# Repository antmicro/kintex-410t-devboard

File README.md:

# Kintex K410T Devboard

Copyright (c) 2022-2025 [Antmicro](https://www.antmicro.com)

## Overview

This repository contains open hardware design files for a devkit created for AMD-Xilinx [Kintex-7 K410T](https://www.xilinx.com/products/silicon-devices/fpga/kintex-7.html) FPGA.

This development board routes the I/O interfaces from the SoM and provides the necessary power buses.
The design files were prepared in KiCad 7.

## Repository structure

The main repository directory contains KiCad PCB project files, a [LICENSE](LICENSE), and a README.
The remaining files are stored in the following directories:

* `doc` - contains generated schematics and other documentation
* `img` - contains graphics for this README
* `assets` - contains visual assets for showcasing the board on Antmicro [Open Hardware Portal](https://openhardware.antmicro.com)

## Key features

* AMD-Xilinx Kintex-7 K410T FPGA
* 512MB of DDR3L memory
* 256MB of SPI NOR flash
* 8MB of SRAM memory
* Assembly option for 2x QSPI
* Gigabit Ethernet
* HDMI output
* USB Type-C connector for FTDI JTAG and debug
* 2x PMOD
* FMC+ connector

## Block diagram

## Licensing

This project is published under the [Apache-2.0](LICENSE) license.

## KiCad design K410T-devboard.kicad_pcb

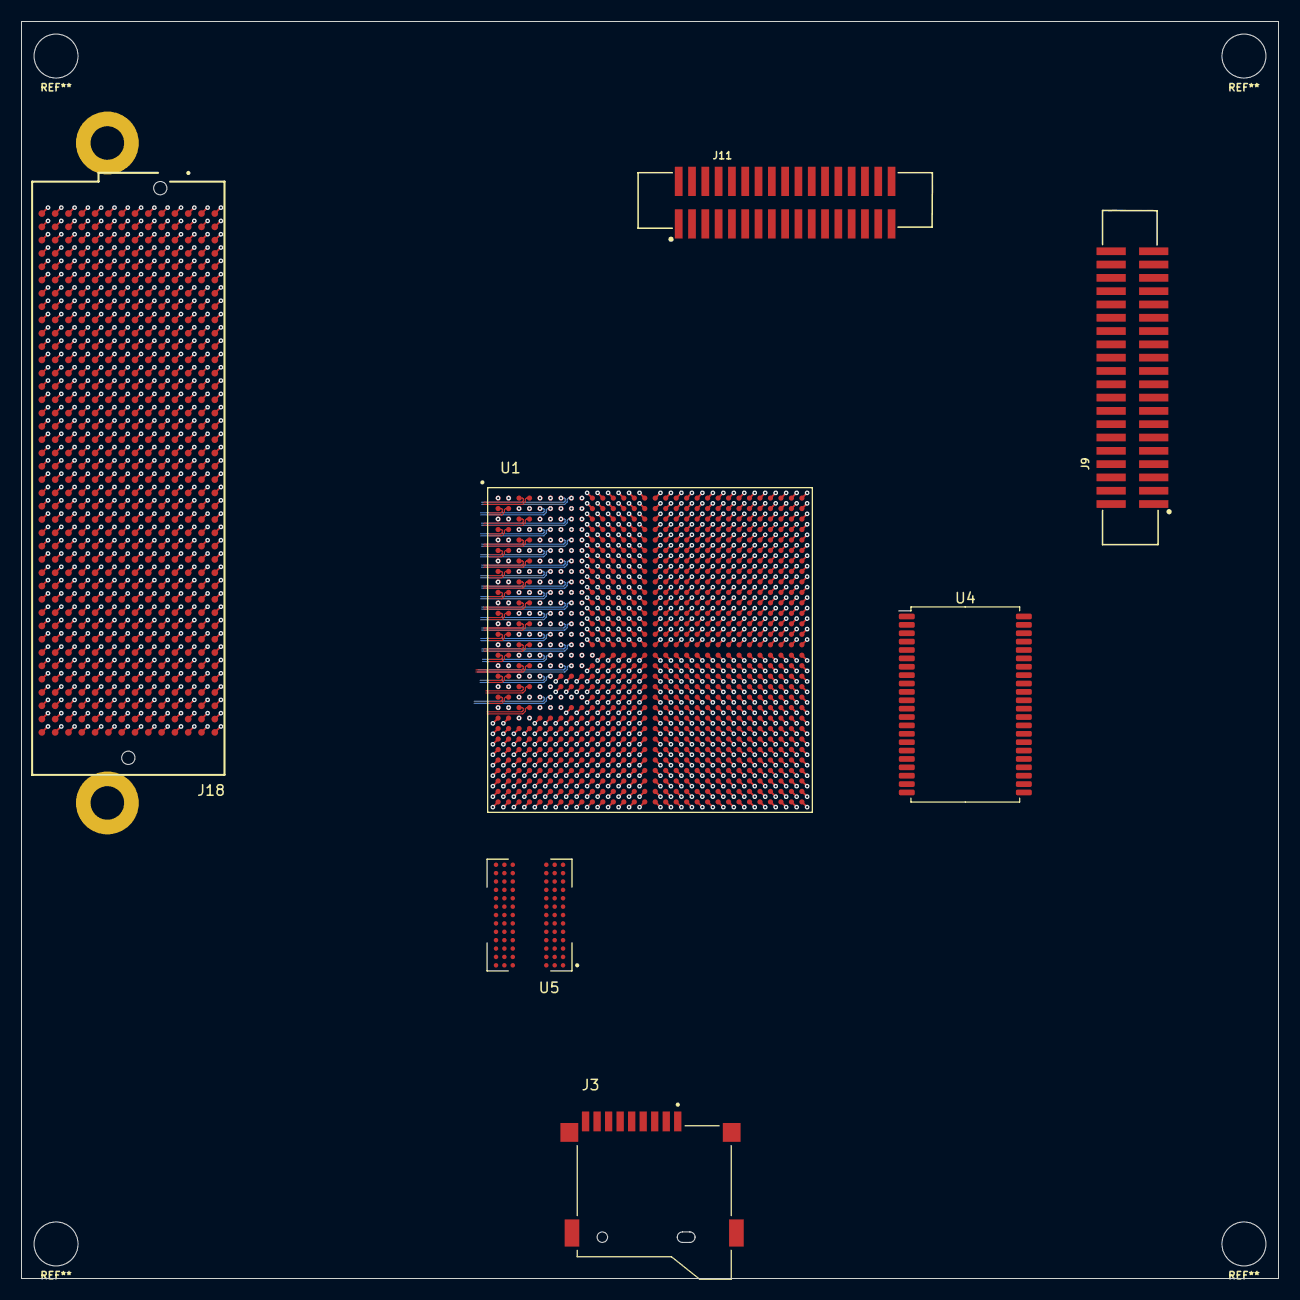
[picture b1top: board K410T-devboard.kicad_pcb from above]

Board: 10 copper layers, 120.0 x 120.0 mm, 7 parts (0 on the bottom side), 213 nets.

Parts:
J3: 693071020811; WE_693071020811
J9: 62704020621; 627x4020621
J11: 62703420621; 627x3420621
J18: ASP-184329-01_mounting_holes_FMCPinout; ASP-184329-01_mounting_holes
U1: XC7K410T-2FFG900I; xc7k410t-2ffg900I
U4: AS6C8008-55ZIN; TSOP-II-44_10.16x18.41mm_P0.8mm
U5: MT41K512M8DA; Micron_FBGA-78

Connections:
3V3_SYS: J18.C39 (3P3V), J18.D36 (3P3V), J18.D38 (3P3V), J18.D40 (3P3V)
12P0V: J18.C35 (12P0V), J18.C37 (12P0V)
+0V675_VREF: U5.E1 (VREFDQ), U5.J8 (VREFCA)
+0V675_VTT: U1.AD7 (IO_L6N_T0_VREF_34), U1.AG8 (IO_L19N_T3_VREF_34)
+1V0: U1.M11 (VCCINT), U1.M13 (VCCINT), U1.M15 (VCCINT), U1.M17 (VCCINT), U1.N10 (VCCINT), U1.N12 (VCCINT), U1.N14 (VCCINT), U1.N16 (VCCBRAM), U1.N18 (VCCINT), U1.P11 (VCCINT), U1.P17 (VCCINT), U1.R10 (VCCINT), U1.R12 (VCCINT), U1.R16 (VCCBRAM), U1.R18 (VCCINT), U1.T11 (VCCINT), U1.T17 (VCCINT), U1.U10 (VCCINT), U1.U12 (VCCINT), U1.U16 (VCCBRAM), U1.U18 (VCCINT), U1.V17 (VCCINT), U1.W16 (VCCBRAM), U1.W18 (VCCINT)
+1V2_MGTAVCC: U1.B7 (MGTAVCC), U1.D7 (MGTAVCC), U1.F7 (MGTAVCC), U1.H7 (MGTAVCC), U1.K7 (MGTAVCC), U1.M7 (MGTAVCC), U1.P7 (MGTAVCC)
+1V2_MGTAVTT: U1.B3 (MGTAVTT), U1.C5 (MGTAVTT), U1.D3 (MGTAVTT), U1.E5 (MGTAVTT), U1.F3 (MGTAVTT), U1.G5 (MGTAVTT), U1.H3 (MGTAVTT), U1.J5 (MGTAVTT), U1.K3 (MGTAVTT), U1.L5 (MGTAVTT), U1.M3 (MGTAVTT), U1.N5 (MGTAVTT), U1.P3 (MGTAVTT), U1.R5 (MGTAVTT), U1.T3 (MGTAVTT), U1.U5 (MGTAVTT), U1.V3 (MGTAVTT), U1.W5 (MGTAVTT), U1.W7 (MGTAVTTRCAL_115)
+1V8: U1.AA9 (VCCO_33), U1.AA19 (VCCO_32), U1.AB16 (VCCO_32), U1.AC13 (VCCO_33), U1.AD10 (VCCO_33), U1.AE17 (VCCO_32), U1.AF14 (VCCO_32), U1.AG11 (VCCO_33), U1.AH18 (VCCO_32), U1.AJ15 (VCCO_32), U1.AK12 (VCCO_33), U1.P13 (VCCAUX), U1.T7 (MGTVCCAUX), U1.T13 (VCCAUX), U1.V7 (MGTVCCAUX), U1.V11 (VCCAUX_IO_G0), U1.V13 (VCCAUX), U1.V15 (VCCAUX), U1.W10 (VCCAUX_IO_G0), U1.W12 (VCCAUX_IO_G0), U1.W14 (VCCAUX), U1.Y12 (VCCO_33)
+1V35: U1.AC3 (VCCO_34), U1.AE7 (VCCO_34), U1.AF4 (VCCO_34), U1.AG1 (VCCO_34), U1.AH8 (VCCO_34), U1.AJ5 (VCCO_34), U1.AK2 (VCCO_34), U5.A2 (VDD), U5.A9 (VDD), U5.B9 (VDDQ), U5.C1 (VDDQ), U5.D7 (VDD), U5.E2 (VDDQ), U5.E9 (VDDQ), U5.G2 (VDD), U5.G8 (VDD), U5.K1 (VDD), U5.K9 (VDD), U5.M1 (VDD), U5.M9 (VDD)
+3V3: J3.4 (VDD), J9.22, J11.22, U1.AA29 (VCCO_13), U1.AB6 (VCCO_0), U1.AB26 (VCCO_13), U1.AC23 (VCCO_12), U1.AD20 (VCCO_12), U1.AD30 (VCCO_13), U1.AE27 (VCCO_13), U1.AF24 (VCCO_12), U1.AG21 (VCCO_12), U1.AH28 (VCCO_13), U1.AJ25 (VCCO_13), U1.AK22 (VCCO_12), U1.P30 (VCCO_14), U1.R27 (VCCO_14), U1.T9 (VCCO_0), U1.T24 (VCCO_14), U1.U21 (VCCO_14), U1.V28 (VCCO_14), U1.W25 (VCCO_14), U1.Y22 (VCCO_12), U4.11 (VCC), U4.33 (VCC)
/DRAM + SRAM/DDR.A0: U1.AE4 (IO_L10P_T1_34), U5.K3 (A0)
/DRAM + SRAM/DDR.A1: U1.AG3 (IO_L9N_T1_DQS_34), U5.L7 (A1)
/DRAM + SRAM/DDR.A2: U1.AG4 (IO_L9P_T1_DQS_34), U5.L3 (A2)
/DRAM + SRAM/DDR.A3: U1.AF1 (IO_L8N_T1_34), U5.K2 (A3)
/DRAM + SRAM/DDR.A4: U1.AE1 (IO_L8P_T1_34), U5.L8 (A4)
/DRAM + SRAM/DDR.A5: U1.AF2 (IO_L7N_T1_34), U5.L2 (A5)
/DRAM + SRAM/DDR.A6: U1.AF3 (IO_L7P_T1_34), U5.M8 (A6)
/DRAM + SRAM/DDR.A7: U1.AC7 (IO_L6P_T0_34), U5.M2 (A7)
/DRAM + SRAM/DDR.A8: U1.AE6 (IO_L5N_T0_34), U5.N8 (A8)
/DRAM + SRAM/DDR.A9: U1.AD6 (IO_L5P_T0_34), U5.M3 (A9)
/DRAM + SRAM/DDR.A10: U1.AC4 (IO_L4N_T0_34), U5.H7 (A10/AP)
/DRAM + SRAM/DDR.A11: U1.AC5 (IO_L4P_T0_34), U5.M7 (A11)
/DRAM + SRAM/DDR.A12: U1.AC1 (IO_L2N_T0_34), U5.K7 (A12/BC#)
/DRAM + SRAM/DDR.A13: U1.AC2 (IO_L2P_T0_34), U5.N3 (A13)
/DRAM + SRAM/DDR.A14: U1.AD3 (IO_L1N_T0_34), U5.N7 (A14)
/DRAM + SRAM/DDR.A15: U1.AD4 (IO_L1P_T0_34), U5.J7 (A15)
/DRAM + SRAM/DDR.BA0: U1.AF5 (IO_L11N_T1_SRCC_34), U5.J2 (BA0)
/DRAM + SRAM/DDR.BA1: U1.AE5 (IO_L11P_T1_SRCC_34), U5.K8 (BA1)
/DRAM + SRAM/DDR.BA2: U1.AE3 (IO_L10N_T1_34), U5.J3 (BA2)
/DRAM + SRAM/DDR.CKE: U1.AH2 (IO_L16P_T2_34), U5.G9 (CKE)
/DRAM + SRAM/DDR.CK_N: U1.AD1 (IO_L3N_T0_DQS_34), U5.G7 (CK#)
/DRAM + SRAM/DDR.CK_P: U1.AD2 (IO_L3P_T0_DQS_34), U5.F7 (CK)
/DRAM + SRAM/DDR.DM: U1.AF8 (IO_L19P_T3_34), U5.B7 (DM/TDQS)
/DRAM + SRAM/DDR.DQ0: U1.AK5 (IO_L24P_T3_34), U5.B3 (DQ0)
/DRAM + SRAM/DDR.DQ1: U1.AK8 (IO_L23N_T3_34), U5.C7 (DQ1)
/DRAM + SRAM/DDR.DQ2: U1.AK6 (IO_L22N_T3_34), U5.C2 (DQ2)
/DRAM + SRAM/DDR.DQ3: U1.AJ6 (IO_L22P_T3_34), U5.C8 (DQ3)
/DRAM + SRAM/DDR.DQ4: U1.AG7 (IO_L20N_T3_34), U5.E3 (NF/DQ4)
/DRAM + SRAM/DDR.DQ5: U1.AJ8 (IO_L23P_T3_34), U5.E8 (NF/DQ5)
/DRAM + SRAM/DDR.DQ6: U1.AK4 (IO_L24N_T3_34), U5.D2 (NF/DQ6)
/DRAM + SRAM/DDR.DQ7: U1.AF7 (IO_L20P_T3_34), U5.E7 (NF/DQ7)
/DRAM + SRAM/DDR.DQS_N: U1.AJ7 (IO_L21N_T3_DQS_34), U5.D3 (DQS#)
/DRAM + SRAM/DDR.DQS_P: U1.AH7 (IO_L21P_T3_DQS_34), U5.C3 (DQS)
/DRAM + SRAM/DDR.ODT: U1.AJ2 (IO_L16N_T2_34), U5.G1 (ODT)
/DRAM + SRAM/DDR.~CAS: U1.AF6 (IO_L12P_T1_MRCC_34), U5.G3 (CAS#)
/DRAM + SRAM/DDR.~CS: U1.AH1 (IO_L15N_T2_DQS_34), U5.H2 (CS#)
/DRAM + SRAM/DDR.~RAS: U1.AG5 (IO_L12N_T1_MRCC_34), U5.F3 (RAS#)
/DRAM + SRAM/DDR.~RESET: U1.AH4 (IO_L13P_T2_MRCC_34), U5.N2 (RESET#)
/DRAM + SRAM/DDR.~WE: U1.AG2 (IO_L15P_T2_DQS_34), U5.H3 (WE#)
/DRAM + SRAM/SRAM.A0: U1.U28 (IO_L13N_T2_MRCC_14), U4.5 (A0)
/DRAM + SRAM/SRAM.A1: U1.V29 (IO_L17P_T2_A14_D30_14), U4.4 (A1)
/DRAM + SRAM/SRAM.A2: U1.T25 (IO_L14P_T2_SRCC_14), U4.3 (A2)
/DRAM + SRAM/SRAM.A3: U1.T26 (IO_L12P_T1_MRCC_14), U4.2 (A3)
/DRAM + SRAM/SRAM.A4: U1.V20 (IO_L19N_T3_A09_D25_VREF_14), U4.1 (A4)
/DRAM + SRAM/SRAM.A5: U1.P27 (IO_L8P_T1_D11_14), U4.44 (A5)
/DRAM + SRAM/SRAM.A6: U1.P28 (IO_L8N_T1_D12_14), U4.43 (A6)
/DRAM + SRAM/SRAM.A7: U1.V24 (IO_L23N_T3_A02_D18_14), U4.42 (A7)
/DRAM + SRAM/SRAM.A8: U1.R26 (IO_L10N_T1_D15_14), U4.39 (A8)
/DRAM + SRAM/SRAM.A9: U1.R30 (IO_L9P_T1_DQS_14), U4.28 (A9)
/DRAM + SRAM/SRAM.A10: U1.U27 (IO_L13P_T2_MRCC_14), U4.27 (A10)
/DRAM + SRAM/SRAM.A11: U1.U25 (IO_L14N_T2_SRCC_14), U4.26 (A11)
/DRAM + SRAM/SRAM.A12: U1.V19 (IO_L19P_T3_A10_D26_14), U4.25 (A12)
/DRAM + SRAM/SRAM.A13: U1.T27 (IO_L12N_T1_MRCC_14), U4.24 (A13)
/DRAM + SRAM/SRAM.A14: U1.U23 (IO_L21N_T3_DQS_A06_D22_14), U4.23 (A14)
/DRAM + SRAM/SRAM.A15: U1.T30 (IO_L9N_T1_DQS_D13_14), U4.22 (A15)
/DRAM + SRAM/SRAM.A16: U1.W23 (IO_L20P_T3_A08_D24_14), U4.21 (A16)
/DRAM + SRAM/SRAM.A17: U1.W24 (IO_L20N_T3_A07_D23_14), U4.20 (A17)
/DRAM + SRAM/SRAM.A18: U1.V25 (IO_L18P_T2_A12_D28_14), U4.19 (A18)
/DRAM + SRAM/SRAM.A19: U1.W26 (IO_L18N_T2_A11_D27_14), U4.18 (A19)
/DRAM + SRAM/SRAM.CE2: U1.U22 (IO_L21P_T3_DQS_14), U4.40 (CE2)
/DRAM + SRAM/SRAM.DQ0: U1.V21 (IO_L22P_T3_A05_D21_14), U4.9 (DQ0)
/DRAM + SRAM/SRAM.DQ1: U1.V30 (IO_L17N_T2_A13_D29_14), U4.10 (DQ1)
/DRAM + SRAM/SRAM.DQ2: U1.W21 (IO_L24P_T3_A01_D17_14), U4.13 (DQ2)
/DRAM + SRAM/SRAM.DQ3: U1.P29 (IO_L7P_T1_D09_14), U4.14 (DQ3)
/DRAM + SRAM/SRAM.DQ4: U1.U20 (IO_L6N_T0_D08_VREF_14), U4.31 (DQ4)
/DRAM + SRAM/SRAM.DQ5: U1.T28 (IO_L11N_T1_SRCC_14), U4.32 (DQ5)
/DRAM + SRAM/SRAM.DQ6: U1.R28 (IO_L11P_T1_SRCC_14), U4.35 (DQ6)
/DRAM + SRAM/SRAM.DQ7: U1.R29 (IO_L7N_T1_D10_14), U4.36 (DQ7)
/DRAM + SRAM/SRAM.~CE: U1.V27 (IO_L16N_T2_A15_D31_14), U4.6 (CE#)
/DRAM + SRAM/SRAM.~OE: U1.P26 (IO_L10P_T1_D14_14), U4.41 (OE#)
/DRAM + SRAM/SRAM.~WE: U1.W22 (IO_L24N_T3_A00_D16_14), U4.17 (WE#)
/FMC+ HSPC/FMC.IO0: J18.G33 (LA31_P), U1.G12 (IO0_18)
/FMC+ HSPC/FMC.IO1_N: J18.G22 (LA20_N), U1.K16 (IOL1N_T0_18)
/FMC+ HSPC/FMC.IO1_P: J18.G21 (LA20_P), U1.L16 (IOL1P_T0_18)
/FMC+ HSPC/FMC.IO2_N: J18.G19 (LA16_N), U1.K15 (IOL2N_T0_18)
/FMC+ HSPC/FMC.IO2_P: J18.G18 (LA16_P), U1.L15 (IOL2P_T0_18)
/FMC+ HSPC/FMC.IO3_N: J18.H20 (LA15_N), U1.L13 (IOL3N_T0_DQS_18)
/FMC+ HSPC/FMC.IO3_P: J18.H19 (LA15_P), U1.L12 (IOL3P_T0_DQS_18)
/FMC+ HSPC/FMC.IO4_N: J18.H17 (LA11_N), U1.J13 (IOL4N_T0_18)
/FMC+ HSPC/FMC.IO4_P: J18.H16 (LA11_P), U1.K13 (IOL4P_T0_18)
/FMC+ HSPC/FMC.IO5_N: J18.J19 (HA18_N), U1.J14 (IOL5N_T0_18)
/FMC+ HSPC/FMC.IO5_P: J18.J18 (HA18_P), U1.K14 (IOL5P_T0_18)
/FMC+ HSPC/FMC.IO6_N: J18.G25 (LA22_N), U1.K11 (IOL6N_T0_VREF_18)
/FMC+ HSPC/FMC.IO6_P: J18.G24 (LA22_P), U1.L11 (IOL6P_T0_18)
/FMC+ HSPC/FMC.IO7_N: J18.H29 (LA24_N), U1.G15 (IOL7N_T1_18)
/FMC+ HSPC/FMC.IO7_P: J18.H28 (LA24_P), U1.H15 (IOL7P_T1_18)
/FMC+ HSPC/FMC.IO8_N: J18.G28 (LA25_N), U1.J12 (IOL8N_T1_18)
/FMC+ HSPC/FMC.IO8_P: J18.G27 (LA25_P), U1.J11 (IOL8P_T1_18)
/FMC+ HSPC/FMC.IO9_N: J18.G31 (LA29_N), U1.H16 (IOL9N_T1_DQS_18)
/FMC+ HSPC/FMC.IO9_P: J18.G30 (LA29_P), U1.J16 (IOL9P_T1_DQS_18)
/FMC+ HSPC/FMC.IO10_N: J18.H26 (LA21_N), U1.H12 (IOL10N_T1_18)
/FMC+ HSPC/FMC.IO10_P: J18.H25 (LA21_P), U1.H11 (IOL10P_T1_18)
/FMC+ HSPC/FMC.IO11_N: J18.K23 (HA23_N), U1.G14 (IOL11N_T1_SRCC_18)
/FMC+ HSPC/FMC.IO11_P: J18.K22 (HA23_P), U1.H14 (IOL11P_T1_SRCC_18)
/FMC+ HSPC/FMC.IO12_N: J18.J22 (HA22_N), U1.F13 (IOL12N_T1_MRCC_18)
/FMC+ HSPC/FMC.IO12_P: J18.J21 (HA22_P), U1.G13 (IOL12P_T1_MRCC_18)
/FMC+ HSPC/FMC.IO13_N: J18.K20 (HA21_N), U1.D13 (IOL13N_T2_MRCC_18)
/FMC+ HSPC/FMC.IO13_P: J18.K19 (HA21_P), U1.D12 (IOL13P_T2_MRCC_18)
/FMC+ HSPC/FMC.IO14_N: J18.J25 (HB01_N), U1.E13 (IOL14N_T2_SRCC_18)
/FMC+ HSPC/FMC.IO14_P: J18.J24 (HB01_P), U1.F12 (IOL14P_T2_SRCC_18)
/FMC+ HSPC/FMC.IO16_N: J18.K08 (HA02_N), U1.E11 (IOL16N_T2_18)
/FMC+ HSPC/FMC.IO16_P: J18.K07 (HA02_P), U1.F11 (IOL16P_T2_18)
/FMC+ HSPC/FMC.IO17_N: J18.K17 (HA17_N_CC), U1.A12 (IOL17N_T2_18)
/FMC+ HSPC/FMC.IO17_P: J18.K16 (HA17_P_CC), U1.A11 (IOL17P_T2_18)
/FMC+ HSPC/FMC.IO18_N: J18.J10 (HA07_N), U1.C11 (IOL18N_T2_18)
/FMC+ HSPC/FMC.IO18_P: J18.J09 (HA07_P), U1.D11 (IOL18P_T2_18)
/FMC+ HSPC/FMC.IO19_N: J18.H23 (LA19_N), U1.E16 (IOL19N_T3_VREF_18)
/FMC+ HSPC/FMC.IO19_P: J18.H22 (LA19_P), U1.F15 (IOL19P_T3_18)
/FMC+ HSPC/FMC.IO20_N: J18.K26 (HB00_N_CC), U1.E15 (IOL20N_T3_18)
/FMC+ HSPC/FMC.IO20_P: J18.K25 (HB00_P_CC), U1.E14 (IOL20P_T3_18)
/FMC+ HSPC/FMC.IO21_N: J18.K11 (HA06_N), U1.C14 (IOL21N_T3_DQS_18)
/FMC+ HSPC/FMC.IO21_P: J18.K10 (HA06_P), U1.D14 (IOL21P_T3_DQS_18)
/FMC+ HSPC/FMC.IO23_N: J18.J13 (HA11_N), U1.B15 (IOL23N_T3_18)
/FMC+ HSPC/FMC.IO23_P: J18.J12 (HA11_P), U1.C15 (IOL23P_T3_18)
/FMC+ HSPC/FMC.IO24_N: J18.J28 (HB07_N), U1.A15 (IOL24N_T3_18)
/FMC+ HSPC/FMC.IO24_P: J18.J27 (HB07_P), U1.B14 (IOL24P_T3_18)
/FMC+ HSPC/FMC.IO25: J18.K28 (HB06_P_CC), U1.F16 (IO25_18)
/FMC+ HSPC/GTX115.RX0_N: J18.B13 (DP7_M2C_N), U1.AA3 (MGTXRXN0_115)
/FMC+ HSPC/GTX115.RX0_P: J18.B12 (DP7_M2C_P), U1.AA4 (MGTXRXP0_115)
/FMC+ HSPC/GTX115.RX1_N: J18.B17 (DP6_M2C_N), U1.Y5 (MGTXRXN1_115)
/FMC+ HSPC/GTX115.RX1_P: J18.B16 (DP6_M2C_P), U1.Y6 (MGTXRXP1_115)
/FMC+ HSPC/GTX115.RX2_N: J18.A19 (DP5_M2C_N), U1.W3 (MGTXRXN2_115)
/FMC+ HSPC/GTX115.RX2_P: J18.A18 (DP5_M2C_P), U1.W4 (MGTXRXP2_115)
/FMC+ HSPC/GTX115.RX3_N: J18.A15 (DP4_M2C_N), U1.V5 (MGTXRXN3_115)
/FMC+ HSPC/GTX115.RX3_P: J18.A14 (DP4_M2C_P), U1.V6 (MGTXRXP3_115)
/FMC+ HSPC/GTX116.RX0_N: J18.A11 (DP3_M2C_N), U1.T5 (MGTXRXN0_116)
/FMC+ HSPC/GTX116.RX0_P: J18.A10 (DP3_M2C_P), U1.T6 (MGTXRXP0_116)
/FMC+ HSPC/GTX116.RX1_N: J18.A07 (DP2_M2C_N), U1.R3 (MGTXRXN1_116)
/FMC+ HSPC/GTX116.RX1_P: J18.A06 (DP2_M2C_P), U1.R4 (MGTXRXP1_116)
/FMC+ HSPC/GTX116.RX2_N: J18.A03 (DP1_M2C_N), U1.P5 (MGTXRXN2_116)
/FMC+ HSPC/GTX116.RX2_P: J18.A02 (DP1_M2C_P), U1.P6 (MGTXRXP2_116)
/FMC+ HSPC/GTX116.RX3_N: J18.C07 (DP0_M2C_N), U1.M5 (MGTXRXN3_116)
/FMC+ HSPC/GTX116.RX3_P: J18.C06 (DP0_M2C_P), U1.M6 (MGTXRXP3_116)
/FPGA Bank 33/SD_CARD.CLK: J3.5 (CLK), U1.AC11 (IO_L9N_T1_DQS_33)
/FPGA Bank 33/SD_CARD.CMD: J3.3 (CMD), U1.AC10 (IO_L7N_T1_33)
/FPGA Bank 33/SD_CARD.DAT0: J3.7 (DAT0), U1.AK14 (IO_L20P_T3_33)
/FPGA Bank 33/SD_CARD.DAT1: J3.8 (DAT1), U1.AF11 (IO_L11N_T1_SRCC_33)
/FPGA Bank 33/SD_CARD.DAT2: J3.1 (DAT2), U1.AE9 (IO_L10N_T1_33)
/FPGA Bank 33/SD_CARD.DAT3: J3.2 (DAT3/CD), U1.AB10 (IO_L7P_T1_33)
/USER_IO.A1: J9.1, U1.M19 (IO_0_15)
/USER_IO.A3: J9.3, U1.L30 (IO_L9P_T1_DQS_AD11P_15)
/USER_IO.A5: J9.5, U1.P21 (IO_L22P_T3_A17_15)
/USER_IO.A7: J9.7, U1.N20 (IO_L19N_T3_A21_VREF_15)
/USER_IO.A9: J9.9, U1.J29 (IO_L7P_T1_AD10P_15)
/USER_IO.A11: J9.11, U1.M28 (IO_L14P_T2_SRCC_15)
/USER_IO.A12: J9.12, U1.J27 (IO_L8P_T1_AD3P_15)
/USER_IO.A13: J9.13, U1.H29 (IO_L7N_T1_AD10N_15)
/USER_IO.A14: J9.14, U1.J28 (IO_L8N_T1_AD3N_15)
/USER_IO.A15: J9.15, U1.N19 (IO_L19P_T3_A22_15)
/USER_IO.A16: J9.16, U1.M20 (IO_L6P_T0_15)
/USER_IO.A17: J9.17, U1.J26 (IO_L10N_T1_AD4N_15)
/USER_IO.A18: J9.18, U1.L20 (IO_L6N_T0_VREF_15)
/USER_IO.A21: J9.21, U1.M27 (IO_L16N_T2_A27_15)
/USER_IO.A23: J9.23, U1.M29 (IO_L15P_T2_DQS_15)
/USER_IO.A24: J9.24, U1.N30 (IO_L17N_T2_A25_15)
/USER_IO.A25: J9.25, U1.L21 (IO_L4P_T0_AD9P_15)
/USER_IO.A26: J9.26, U1.J22 (IO_L5N_T0_AD2N_15)
/USER_IO.A27: J9.27, U1.P22 (IO_L22N_T3_A16_15)
/USER_IO.A28: J9.28, U1.M30 (IO_L15N_T2_DQS_ADV_B_15)
/USER_IO.A29: J9.29, U1.M23 (IO_L24N_T3_RS0_15)
/USER_IO.A30: J9.30, U1.N27 (IO_L16P_T2_A28_15)
/USER_IO.A31: J9.31, U1.L26 (IO_L11P_T1_SRCC_AD12P_15)
/USER_IO.A32: J9.32, U1.K28 (IO_L13P_T2_MRCC_15)
/USER_IO.A33: J9.33, U1.L28 (IO_L14N_T2_SRCC_15)
/USER_IO.A35: J9.35, U1.L25 (IO_L12P_T1_MRCC_AD5P_15)
/USER_IO.A36: J9.36, U1.N29 (IO_L17P_T2_A26_15)
/USER_IO.A37: J9.37, U1.L27 (IO_L11N_T1_SRCC_AD12N_15)
/USER_IO.A38: J9.38, U1.N26 (IO_L18N_T2_A23_15)
/USER_IO.A39: J9.39, U1.K26 (IO_L10P_T1_AD4P_15)
/USER_IO.A40: J9.40, U1.K21 (IO_L4N_T0_AD9N_15)
/USER_IO.B1: J11.1, U1.D27 (IO_L13P_T2_MRCC_16)
/USER_IO.B3: J11.3, U1.A30 (IO_L17N_T2_16)
/USER_IO.B5: J11.5, U1.H25 (IO_L19N_T3_VREF_16)
/USER_IO.B6: J11.6, U1.C26 (IO_L11N_T1_SRCC_16)
/USER_IO.B7: J11.7, U1.E29 (IO_L18P_T2_16)
/USER_IO.B8: J11.8, U1.A23 (IO_L1N_T0_16)
/USER_IO.B9: J11.9, U1.A28 (IO_L9N_T1_DQS_16)
/USER_IO.B10: J11.10, U1.A27 (IO_L7N_T1_16)
/USER_IO.B11: J11.11, U1.A26 (IO_L10N_T1_16)
/USER_IO.B12: J11.12, U1.B27 (IO_L7P_T1_16)
/USER_IO.B14: J11.14, U1.C25 (IO_L12P_T1_MRCC_16)
/USER_IO.B15: J11.15, U1.B28 (IO_L9P_T1_DQS_16)
/USER_IO.B16: J11.16, U1.B24 (IO_L8N_T1_16)
/USER_IO.B17: J11.17, U1.G29 (IO_L22P_T3_16)
/USER_IO.B18: J11.18, U1.C24 (IO_L8P_T1_16)
/USER_IO.B19: J11.19, U1.F30 (IO_L22N_T3_16)
/USER_IO.B21: J11.21, U1.F28 (IO_L20N_T3_16)
/USER_IO.B23: J11.23, U1.G28 (IO_L20P_T3_16)
/USER_IO.B24: J11.24, U1.A25 (IO_L10P_T1_16)
/USER_IO.B25: J11.25, U1.G30 (IO_L24N_T3_16)
/USER_IO.B26: J11.26, U1.B25 (IO_L12N_T1_MRCC_16)
/USER_IO.B27: J11.27, U1.H30 (IO_L24P_T3_16)
/USER_IO.B28: J11.28, U1.E30 (IO_L18N_T2_16)
/USER_IO.B29: J11.29, U1.H24 (IO_L19P_T3_16)
/USER_IO.B30: J11.30, U1.C27 (IO_L13N_T2_MRCC_16)
/USER_IO.B31: J11.31, U1.F27 (IO_L21N_T3_DQS_16)
/USER_IO.B33: J11.33, U1.G27 (IO_L21P_T3_DQS_16)
EP: J3.6 (VSS), J9.2, J9.4, J9.6, J9.8, J9.10, J9.20, J9.34, J11.2, J11.4, J11.20, J18.A01 (GND), J18.A04 (GND), J18.A05 (GND), J18.A08 (GND), J18.A09 (GND), J18.A12 (GND), J18.A13 (GND), J18.A16 (GND), J18.A17 (GND), J18.A20 (GND), J18.A21 (GND), J18.A24 (GND), J18.A25 (GND), J18.A28 (GND), J18.A29 (GND), J18.A32 (GND), J18.A33 (GND), J18.A36 (GND), J18.A37 (GND), J18.A40 (GND), J18.B02 (GND), J18.B03 (GND), J18.B06 (GND), J18.B07 (GND), J18.B10 (GND), J18.B11 (GND), J18.B14 (GND), J18.B15 (GND), J18.B18 (GND), J18.B19 (GND), J18.B22 (GND), J18.B23 (GND), J18.B26 (GND), J18.B27 (GND), J18.B30 (GND), J18.B31 (GND), J18.B34 (GND), J18.B35 (GND), J18.B38 (GND), J18.B39 (GND), J18.C01 (GND), J18.C04 (GND), J18.C05 (GND), J18.C08 (GND), J18.C09 (GND), J18.C12 (GND), J18.C13 (GND), J18.C16 (GND), J18.C17 (GND), J18.C20 (GND), J18.C21 (GND), J18.C24 (GND), J18.C25 (GND), J18.C28 (GND), J18.C29 (GND), J18.C32 (GND), J18.C33 (GND), J18.C36 (GND), J18.C38 (GND), J18.C40 (GND), J18.D02 (GND), J18.D03 (GND), J18.D06 (GND), J18.D07 (GND), J18.D10 (GND), J18.D13 (GND), J18.D16 (GND), J18.D19 (GND), J18.D22 (GND), J18.D25 (GND), J18.D28 (GND), J18.D37 (GND), J18.D39 (GND), J18.E01 (GND), J18.E04 (GND), J18.E05 (GND), J18.E08 (GND), J18.E11 (GND), J18.E14 (GND), J18.E17 (GND), J18.E20 (GND), J18.E23 (GND), J18.E26 (GND), J18.E29 (GND), J18.E32 (GND), J18.E35 (GND), J18.E38 (GND), J18.E40 (GND), J18.F02 (GND), J18.F03 (GND), J18.F06 (GND), J18.F09 (GND), J18.F12 (GND), J18.F15 (GND), J18.F18 (GND), J18.F21 (GND), J18.F24 (GND), J18.F27 (GND), J18.F30 (GND), J18.F33 (GND), J18.F36 (GND), J18.F39 (GND), J18.G01 (GND), J18.G04 (GND), J18.G05 (GND), J18.G08 (GND), J18.G11 (GND), J18.G14 (GND), J18.G17 (GND), J18.G20 (GND), J18.G23 (GND), J18.G26 (GND), J18.G29 (GND), J18.G32 (GND), J18.G35 (GND), J18.G38 (GND), J18.G40 (GND), J18.H03 (GND), J18.H06 (GND), J18.H09 (GND), J18.H12 (GND), J18.H15 (GND), J18.H18 (GND), J18.H21 (GND), J18.H24 (GND), J18.H27 (GND), J18.H30 (GND), J18.H33 (GND), J18.H36 (GND), J18.H39 (GND), J18.J01 (GND), J18.J04 (GND), J18.J05 (GND), J18.J08 (GND), J18.J11 (GND), J18.J14 (GND), J18.J17 (GND), J18.J20 (GND), J18.J23 (GND), J18.J26 (GND), J18.J29 (GND), J18.J32 (GND), J18.J35 (GND), J18.J38 (GND), J18.J40 (GND), J18.K02 (GND), J18.K03 (GND), J18.K06 (GND), J18.K09 (GND), J18.K12 (GND), J18.K15 (GND), J18.K18 (GND), J18.K21 (GND), J18.K24 (GND), J18.K27 (GND), J18.K30 (GND), J18.K33 (GND), J18.K36 (GND), J18.K39 (GND), U1.A1 (GND), U1.A2 (GND), U1.A5 (GND), U1.A6 (GND), U1.A9 (GND), U1.A14 (GND), U1.A24 (GND), U1.AA1 (GND), U1.AA2 (GND), U1.AA5 (GND), U1.AA6 (GND), U1.AA7 (GND), U1.AA14 (GND), U1.AA24 (GND), U1.AB3 (GND), U1.AB4 (GND), U1.AB11 (GND), U1.AB21 (GND), U1.AC8 (GND), U1.AC18 (GND), U1.AC28 (GND), U1.AD5 (GND), U1.AD15 (GND), U1.AD25 (GND), U1.AE2 (GND), U1.AE12 (GND), U1.AE22 (GND), U1.AF9 (GND), U1.AF19 (GND), U1.AF29 (GND), U1.AG6 (GND), U1.AG16 (GND), U1.AG26 (GND), U1.AH3 (GND), U1.AH13 (GND), U1.AH23 (GND), U1.AJ10 (GND), U1.AJ20 (GND), U1.AJ30 (GND), U1.AK7 (GND), U1.AK17 (GND), U1.AK27 (GND), U1.B4 (GND), U1.B8 (GND), U1.B9 (GND), U1.B11 (GND), U1.B21 (GND), U1.C1 (GND), U1.C2 (GND), U1.C6 (GND), U1.C9 (GND), U1.C18 (GND), U1.C28 (GND), U1.D4 (GND), U1.D8 (GND), U1.D9 (GND), U1.D15 (GND), U1.D25 (GND), U1.E1 (GND), U1.E2 (GND), U1.E6 (GND), U1.E9 (GND), U1.E12 (GND), U1.E22 (GND), U1.F4 (GND), U1.F8 (GND), U1.F9 (GND), U1.F19 (GND), U1.F29 (GND), U1.G1 (GND), U1.G2 (GND), U1.G6 (GND), U1.G9 (GND), U1.G16 (GND), U1.G26 (GND), U1.H4 (GND), U1.H8 (GND), U1.H9 (GND), U1.H13 (GND), U1.H23 (GND), U1.J1 (GND), U1.J2 (GND), U1.J6 (GND), U1.J9 (GND), U1.J10 (GND), U1.J20 (GND), U1.J30 (GND), U1.K4 (GND), U1.K8 (GND), U1.K9 (GND), U1.K17 (GND), U1.K27 (GND), U1.L1 (GND), U1.L2 (GND), U1.L6 (GND), U1.L9 (GND), U1.L14 (GND), U1.L24 (GND), U1.M4 (GND), U1.M8 (GND), U1.M9 (GND), U1.M12 (GND), U1.M14 (GND), U1.M16 (GND), U1.M18 (GND), U1.M21 (GND), U1.N1 (GND), U1.N2 (GND), U1.N6 (GND), U1.N9 (GND), U1.N11 (GND), U1.N13 (GND), U1.N15 (GND), U1.N17 (GND), U1.N28 (GND), U1.P4 (GND), U1.P8 (GND), U1.P9 (GND), U1.P10 (GND), U1.P12 (GND), U1.P14 (GNDADC_0), U1.P16 (GND), U1.P18 (GND), U1.P25 (GND), U1.R1 (GND), U1.R2 (GND), U1.R6 (GND), U1.R9 (GND), U1.R11 (GND), U1.R13 (GND), U1.R14 (VREFN_0), U1.R17 (GND), U1.R22 (GND), U1.T4 (GND), U1.T8 (GND), U1.T10 (GND), U1.T12 (GND), U1.T16 (GND), U1.T18 (GND), U1.T19 (GND), U1.T29 (GND), U1.U1 (GND), U1.U2 (GND), U1.U6 (GND), U1.U9 (GND), U1.U11 (GND), U1.U13 (GND), U1.U17 (GND), U1.U26 (GND), U1.V4 (GND), U1.V8 (GND), U1.V9 (GND), U1.V10 (GND), U1.V12 (GND), U1.V14 (GND), U1.V16 (GND), U1.V18 (GND), U1.V23 (GND), U1.W1 (GND), U1.W2 (GND), U1.W6 (GND), U1.W9 (GND), U1.W11 (GND), U1.W13 (GND), U1.W15 (GND), U1.W17 (GND), U1.W20 (GND), U1.W30 (GND), U1.Y3 (GND), U1.Y4 (GND), U1.Y7 (GND), U1.Y8 (GND), U1.Y9 (GND), U1.Y17 (GND), U1.Y27 (GND), U4.12 (VSS), U4.34 (VSS), U5.A1 (VSS), U5.A8 (VSS), U5.B1 (VSS), U5.B2 (VSSQ), U5.B8 (VSSQ), U5.C9 (VSSQ), U5.D1 (VSSQ), U5.D8 (VSS), U5.D9 (VSSQ), U5.F2 (VSS), U5.F8 (VSS), U5.J1 (VSS), U5.J9 (VSS), U5.L1 (VSS), U5.L9 (VSS), U5.N1 (VSS), U5.N9 (VSS)
unnamed: J3.10 (GND), J3.11 (GND), J3.12 (GND), J3.13 (GND)
VCCO_15: U1.J25 (VCCO_15), U1.K22 (VCCO_15), U1.L29 (VCCO_15), U1.M26 (VCCO_15), U1.N23 (VCCO_15), U1.P20 (VCCO_15)
VCCO_16: U1.A29 (VCCO_16), U1.B26 (VCCO_16), U1.C23 (VCCO_16), U1.D30 (VCCO_16), U1.E27 (VCCO_16), U1.F24 (VCCO_16), U1.H28 (VCCO_16)
VCCO_17: U1.A19 (VCCO_17), U1.B16 (VCCO_17), U1.D20 (VCCO_17), U1.E17 (VCCO_17), U1.G21 (VCCO_17), U1.H18 (VCCO_17), U1.L19 (VCCO_17)
VCCO_18: U1.C13 (VCCO_18), U1.D10 (VCCO_18), U1.F14 (VCCO_18), U1.G11 (VCCO_18), U1.J15 (VCCO_18), U1.K12 (VCCO_18)

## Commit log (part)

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2022-12-19 Initial commit. Create KiCad project, add .gitignore and LICENSE
2022-12-19 Import EC 8C DRC rule template
2022-12-19 Add mandatory decoupling
2022-12-19 Create nano-ITX board edge, create\ FPGA quadrant-style fanout
2022-12-20 Define DDR3 bus
2022-12-20 Add DDR3L nets, termination and decoupling
2022-12-20 Add SRAM, reorganize SDRAM sheet
2022-12-20 Add SRAM signals to FPGA banks 12-15 sheet
2022-12-20 Connect SRAM to FPGA
2022-12-20 Add README.md
2022-12-20 Remove auto_saved_files
2022-12-20 Unify title block
2022-12-21 Update project files naming, reorganize hierarchical sheet structure, power supply WIP
2022-12-21 Remove old schematic files
2022-12-21 Add SPI-FLASH bus and SPI Flash IC. Connet it to FPGA
2022-12-21 Add JTAG bus. Add labels to FPGA JTAG pins
2022-12-21 Add done, init leds and program_b button
2022-12-23 Add SD-CARD bus. Add user SPI flash, rename main SPI flash bus. Add uSD card slot
2022-12-23 Connect SD_CARD and USR_FLASH_0 to FPGA
2022-12-23 Update system SPI Flash bus name, rearrange sheets
2022-12-23 Update sheets name
2022-12-23 Unify sheets tables, add user-gpio sheet
2022-12-23 Add PMOD connectors, leave place for leds, buttons and dip switches
2022-12-27 Replace resistor ladder with 0402 resistors
2022-12-27 Add TUSB1106 USB xceiver, update bus definitions
2022-12-27 Add HDMI/Ethernet sheet
2022-12-27 Add HDMI connector
2022-12-27 Add bootstrap resistors to ETH PHY IC
2022-12-27 Add todo to HDMI
2022-12-27 Add 1V0 DC-DC, VCCADC and VREFP reference voltages, input jack with reverse polarity protection
2022-12-27 Add RMII bus definition
2022-12-27 Replace labels with power symbols
2022-12-27 Add FMC+ HSPC sheet
2022-12-28 Add leds, buttons and dip-switch
2022-12-28 Add missing DCT 0R, connect 3.3V rail to LAN8720A
2022-12-28 Add RST signal to JTAG bus
2022-12-28 Add FTDI to USB-PHY subsheet
2022-12-28 Minor readability improvement. Add power flags in USB and ETH sheets
2022-12-28 Fix PoE labels in hdmi-ethernet sheet
2022-12-28 Fill title block in fmc-hspc sheet
2022-12-29 Add MGTX bus class and add labels to GTX banks
2022-12-29 Add power supply OR'ing, replace VIN global label with power symbol
2022-12-29 Change +0V675_VTT label to proper power symbol
2022-12-29 Update DDR connection to FPGA
2022-12-29 Update system flash bus unfolded labels
2022-12-29 Add pushbutton ON/OFF controller, tidy up dc-dc sheet
2022-12-29 Connect LED, DIP switch and buttons to FPGA
2022-12-29 Update VTT labels with power symbols on DC-DC sheet
2022-12-29 Remap FMC+ signals to GTX buses
2022-12-29 Connect user buttons and dip switch pullups to 1.8V
2022-12-29 Add missing +0V675_VTT power symbol to DDR termination
2022-12-29 Connect 1V8 to usr USB VCIO and pullups
2022-12-30 Change MGT labels to hierarhical
2022-12-30 Add CW-20PIN connector and connect it to FPGA
2022-12-30 Add clocks schematic to the main sheet
2022-12-30 Add diode temp sensor
2023-01-02 Change power labels from global to proper power labels
2023-01-02 Group FMC+ related subsheets close together
2023-01-02 Improve readability of bus connections to FPGA
2023-01-02 Add clocks bus assigment, FTDI buffering WiP
2023-01-02 Finish FTDI buffering
2023-01-03 Update hierarchical labels from USB-PHY subsheet
2023-01-03 Connect power rails to GBE
2023-01-03 Align resistors reference designators
2023-01-03 Improve designators/values placement
2023-01-03 Unify designators orientation
2023-01-03 Connect 1V8 to SPI flash 0
2023-01-03 Add R0 to FTDI I2C singals behind buffer
2023-01-03 Connect USB_HOST SPI interface to FPGA
2023-01-03 Connect I2C bus
2023-01-03 Fix SPI flash signal labels
2023-01-03 Change I2C spelling to superscript
2023-01-03 Fix system-flash connection to FPGA
2023-01-03 Connect USB_HOST on root schematic
2023-01-03 Re-annotate the schematic. Export changes to PCB
2023-01-03 Start creating PCB technology mock
2023-01-04 Connect FPGA bank 17 and 18 to 3.3V
2023-01-04 Add supervisor MCU subsheet and connectors
2023-01-04 Fix MGAVTT label
2023-01-04 Annotate new parts, sync schematic and PCB
2023-01-04 Update MPM54304GMN symbol FB3 pin type
2023-01-04 Finish placing the decoulplig under FPGA, adjust power planes, color voltage domains
2023-01-04 Replace BRAM 4u7 caps to 0201, optimize decoupling placement
2023-01-04 Update supervisor MCU connectors, apply pinout to connectors
2023-01-05 Update pinout for MCU connectors, extend SUP-MCU bus def
2023-01-05 Add new pinout to sup MCU. Start connecting it to FPGA
2023-01-05 DDR3L orientation try-on
2023-01-09 Add DDR3L decoupling capacitors
2023-01-09 Add system flash DQ2/3 note
2023-01-09 Add SUP MCU controll over USB-C PD RST signal
2023-01-09 Connect SUP MCU CLCK signal to FPGA
2023-01-09 Add to-do to dc-dc sheet
2023-01-09 Final placement for DDR3L, Termination pre-routing, add DQ/DQS 40Ohm custom rules
2023-01-09 Increase DDR3L termination track width
2023-01-09 Fix libraries, sync schematic with PCB
2023-01-09 Fix 1V0 DC-DC label
2023-01-10 Finish connecting MCU
2023-01-10 Connect TEMP_ALERT_N signal to MCU
2023-01-10 Replace two ethernet porst with one dual port
2023-01-10 Replace USB-C connectors with vertical ones
2023-01-10 Replace CW connector with 1.27m pitch
2023-01-10 Fix libs, sync schematic with PCB
2023-01-10 DC-DC sheet grouping and placement on PCB
2023-01-10 Unify used buttons
2023-01-10 Inital connectors placement
2023-01-10 Move FPGA to the left
2023-01-10 Finish DC/DC and PoE placement, connect DDR3L VRP and VRL, remove PoE disable optocoupler
2023-01-10 Manually import changes from pcb-wip branch
2023-01-11 Add FPGA radiator, setup layer stack
2023-01-11 Fix JTAG buffor mixed labels
2023-01-11 Increase 0201 to 0402 components where possible (EIA 0402 footprint)
2023-01-11 Change DDR3L decoupling capacitors to 0402, channg SRAM termiantion to resistor array
2023-01-11 Try-on SRAM routing
2023-01-12 Fix minor label missmatch. Continue placment
2023-01-12 Recalculate impedance for new stackup, move DC-DC area components
2023-01-12 Fix labels missmatch. Finish component grouping
2023-01-13 Change ULS-12/5-D48N-C to ULS-12/8.3-D48N-C
2023-01-13 Import recent changes to PCB
2023-01-13 Implemented fixes after schematic review
2023-01-13 Added 100n + 100R on SD card shield
2023-01-13 Place all components inside PCB outline
2023-01-13 Temporarly hide ref designators
2023-01-13 Reassign netclasses
2023-01-13 Connected DQ2 DQ3 lines of SPI flash to FPGA bank 14
2023-01-16 Improve placement of the GBE and USB Host PHY. Update pinout for better routing
2023-01-16 Continue layout
2023-01-16 Setup and reorganize layer stack
2023-01-16 Added USB power switches on USB HOST and USB USR
2023-01-16 Connected USB PON and DET signals to FPGA
2023-01-16 Removed doubled 10uF on USR_USB VBUS
2023-01-16 Annotated designators for new components
2023-01-16 USR IO fanout from FPGA
2023-01-16 Added PWM fan control signal to FPGA, finished routing of USB PD group, temp sensor and user spi flash 0
2023-01-16 E-fuse placement on PCB
2023-01-16 Divide USR IO track between two layers. Route CW20 header. Improve low-speed layer utilization
2023-01-17 Connect JTAG and CW20pin headers
2023-01-17 Routing DRAM, modified signal mapping on termination resistor ladders
2023-01-17 Route low speed signals
2023-01-17 Finishing routing DQ signals of DRAM
2023-01-17 Place components inside PCB outline
2023-01-17 Matching lengths of DQ signals od DRAM in progress..
2023-01-17 Add FMC+ to do's
2023-01-18 DRAM DQ signals routing and length matching finished
2023-01-18 Finished connecting all signals of DRAM
2023-01-18 Recalculated length matching of DRAM DQ signals including pad to die distances
2023-01-20 Continue SRAM fanout
2023-01-20 Fixes on schematic, aligned bank 13 to grid
2023-01-20 Import low-speed signal routing from pcb-wip
2023-01-20 PCIe routing - checking for signal crossings
2023-01-20 Sync PCB with schematics, add vias to SRAM
2023-01-20 Determined signal paths for PCIe, swapped GTX115.TX signals from 0-1-2-3 to 2-1-3-0, swapped signals on layers between GTX116.TX3 and GTX116.REFCLK0
2023-01-20 Continue SRAM routing
2023-01-20 Resolve DRC errors
2023-01-20 Working on final fixes on PCIe interface signals
2023-01-20 Provided feedpoints for FCM 90ohm diff pairs on FPGA edge
2023-01-20 Update signage
2023-01-20 SRAM initial routing
2023-01-23 Finished FMC signals routing
2023-01-23 Update SRAM termination resistor array connections
2023-01-23 Fix signal mix on FTDI-JTAG buffer. Route half of the SUP MCU traces
2023-01-23 Finish low speed signal routing on top sector
2023-01-23 Fixed signal crossings near J6
2023-01-23 Routed J22 signals
2023-01-23 Sync changes from chematics to PCB
2023-01-23 Connect FMC GND
2023-01-24 Reconnect SPI Flash 0 and RMII
2023-01-24 Finished routing SPI flash chips
2023-01-24 Route GBE, USR USB, SPI to FTDI
2023-01-24 Started layout of DC-DC converter power planes
2023-01-24 Swap GBE pairs for easier routing
2023-01-24 Connect GBE
2023-01-24 Routed U37 and In2.CU power plane
2023-01-24 Finished grounding of FMC connector
2023-01-24 Removed conflict of PCIe signal with logo
2023-01-25 Resolve DRC errors (omit unconnected items)
2023-01-25 Connect FMC 12V diode to VDC instead of VIN
2023-01-25 Make USB e-fuses circuitry more readable. Fix GND via intersecting signal trace
2023-01-25 Improved power routing
2023-01-25 Started routing DC-DC converter low speed signals
2023-01-25 Corrected schematic, changed DRAM pullup array value, removed PWM signal from botton FAN connector
2023-01-25 Finished implementing all changes from sch review
2023-01-25 Updated annotation
2023-01-25 Routed more low speed signals
2023-01-25 Removed duplicate components
2023-01-25 Low speed routing
2023-01-26 Updated PCB from schematic
2023-01-26 Routed power input planes
2023-01-26 Completed routing of nearly all misc signals
2023-01-26 Routed regulators left of DDR RAM
2023-01-27 Final length matching of all DDR3L signals finished
2023-01-27 Completed routing of all signals; Fixed FPGA DDR reference
2023-01-27 Fixed USB PEN signals
2023-01-27 README: review
2023-01-27 Update LICENSE, add 3D render
2023-01-27 Added control signals on FMC connector
2023-01-27 Updated schematic page fields
2023-01-27 Adding JTAG to FMC connector - in progress
2023-01-27 Added JTAG signals on FMC connector in sch
2023-01-27 Wired JTAG RST level shifter
2023-01-27 Finished routing JTAG signals to FMC
2023-01-27 Minor PCB fixes
2023-01-30 Added deadbeef under U8
2023-01-30 Finished placement of designators
2023-01-30 Matched RMII and SD card signal lengths
2023-01-31 Small tweaks on top silkscreen
2023-01-31 Corrected PCB after checking gerbers on EC
2023-02-01 Fixed bottom silkscreen overlaps
2023-02-01 Small tweaks on RMII interface routing
2023-02-01 Marked DNP on PCB
2023-02-01 Bump revision to 1.0.0. Update name on schematic and PCB sheets
2023-02-01 Corrected clearances near POE
2023-02-01 Changed placement of u.fl connector
2023-02-01 Cleaned unconnected traces
2023-02-01 Changed U15 to NCP718
2023-02-01 README: Update 3DVis
2023-02-01 Rescale 3DVis
2023-02-01 Tuned length for low speed ETH and HDMI
2023-02-01 Remapped signals and added 0R - related to U33
2023-08-07 Notes added by 'git notes add'
2023-10-18 Introduce component standardization
2023-10-26 [#50532] Update JST connectors footprints
2024-02-27 [#55729] Fix DM3AT-SF-PEJM5
    Save project as KiCad 7
2024-02-28 [#55729] Update PCB from schemtatic
2024-02-29 [#55729] Fix microchip-ksz9131rnxc
2024-03-01 [#55729] Fix micron-mt41k512m8da-107-xit-p-tr
2024-03-01 [#55729] Fix batch of components Fix ftdi-ft4232h-56q-reel Fix maxim-integrated-max3421eetj Fix maxim-integrated-max16150aut-t Fix maxim-integrated-max1617amee-t Fix micron-mt25ql256aba1ew7-0sit
2024-03-01 [#55729] Fix cnc-tech-2007435-1
2024-03-04 [#55729] Fix samtec-erf5-020-05-0-x-dv
2024-03-04 [#55729] Run loclib
2024-03-07 [#55729] Mark heatsink as DNP
2024-03-07 [#55729] Update pcb from schematic
2024-03-27 Update assets
2024-04-02 [#55729] Switch FPGA symbol to antmicroFPGAChips lib
2024-04-02 [#55729] Globlib; Clean DNP; Realign to grid
2024-04-02 [#55729] Clean schematics/update from lib
2024-04-03 [#55729] Optimize top-level schematic connections
2024-04-03 [#55729] Remove loclib
2024-04-09 [#55729] Correct fp links to .step; clean DRC
2024-09-18 [#65778] Update kintex 410t blender model
